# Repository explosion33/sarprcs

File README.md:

# sasrprcs
2023-2024 SARP RCS Controls / Electronics repository

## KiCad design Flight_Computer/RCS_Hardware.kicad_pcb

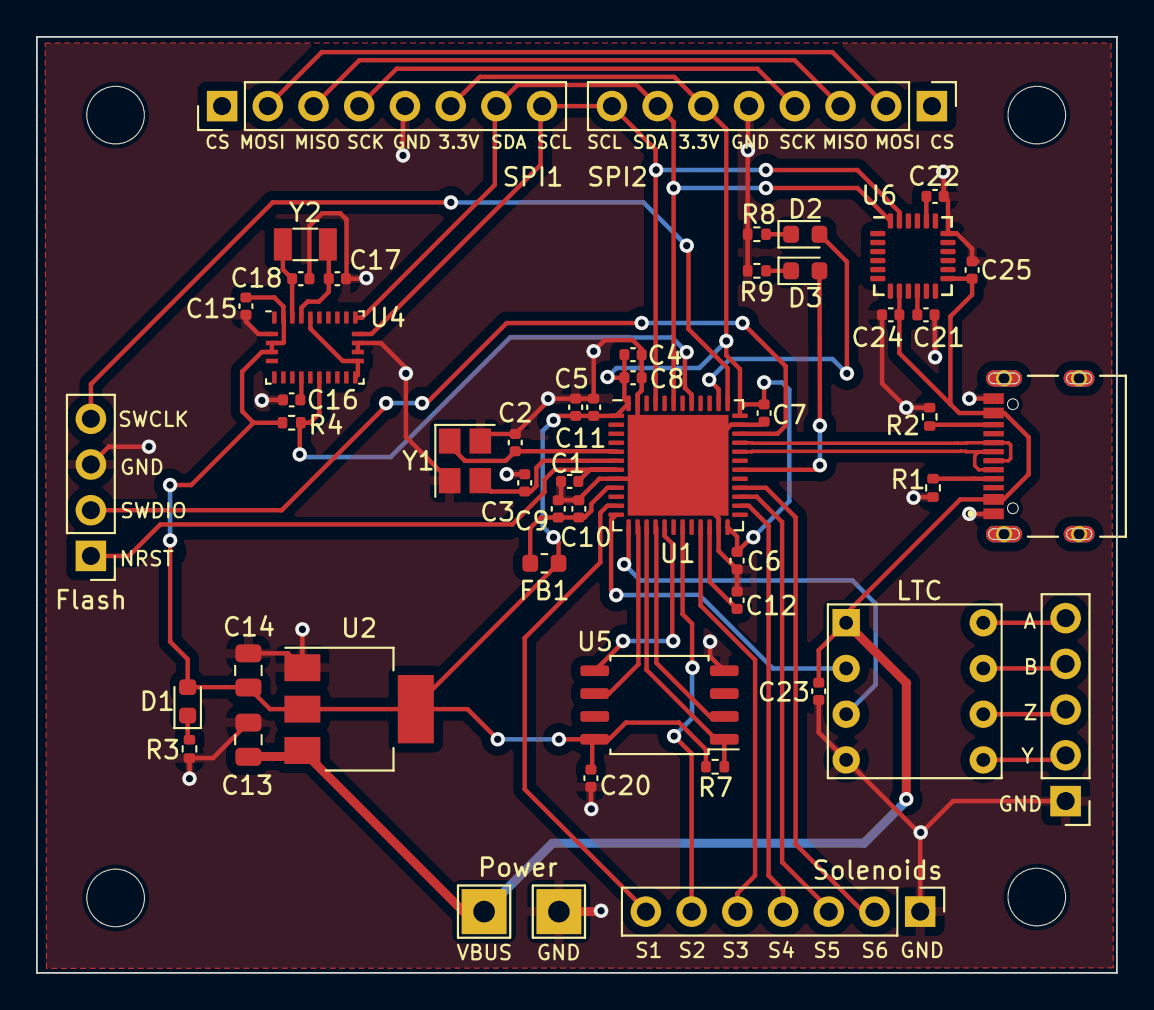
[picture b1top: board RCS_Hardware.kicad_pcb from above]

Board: 2 copper layers, 60.0 x 52.0 mm, 55 parts (0 on the bottom side), 47 nets.

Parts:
C1, C5, C6, C7, C8, C15, C16, C20, C23: 100nF; C_0402_1005Metric
C2, C3: 10pF; C_0402_1005Metric
C4: 10uF; C_0402_1005Metric
C9, C25: 10nF; C_0402_1005Metric
C10, C11: 1uF; C_0402_1005Metric
C12: 2.2uF; C_0402_1005Metric
C13, C14: 22uF; C_0805_2012Metric
C17, C18: 22pF; C_0402_1005Metric
C21, C24: 0.1uF; C_0402_1005Metric
C22: 2.2nF; C_0402_1005Metric
D1, D2, D3: LED; LED_0603_1608Metric
FB1: 120R; L_0603_1608Metric
Flash: SWD; PinHeader_1x04_P2.54mm_Vertical
H1, H2, H3, H4: MountingHole; MountingHole_3.2mm_M3
J2: TYPE-C-31-M-12; HRO_TYPE-C-31-M-12
J4: 5V; TestPoint_THTPad_2.5x2.5mm_Drill1.2mm
J8: Conn_01x05_Male; PinHeader_1x05_P2.54mm_Vertical
LTC: LTC1690N8
Power: GND; TestPoint_THTPad_2.5x2.5mm_Drill1.2mm
R1, R2: 5.11k; R_0402_1005Metric
R3, R8, R9: 1k; R_0402_1005Metric
R4, R7: 10k; R_0402_1005Metric
SPI1, SPI2: SPI; PinHeader_1x08_P2.54mm_Vertical
Solenoids: Solenoids; PinHeader_1x07_P2.54mm_Vertical
U1: STM32F401CCU6; QFN-48-1EP_7x7mm_P0.5mm_EP5.6x5.6mm
U2: AMS1117-3.3; SOT-223-3_TabPin2
U4: BNO055; LGA-28_5.2x3.8mm_P0.5mm
U5: W25Q32JVSS; SOIC-8_5.23x5.23mm_P1.27mm
U6: MPU-6050; InvenSense_QFN-24_4x4mm_P0.5mm
Y1: 16MHz; Crystal_SMD_3225-4Pin_3.2x2.5mm
Y2: 32.768Mhz; Crystal_SMD_3215-2Pin_3.2x1.5mm

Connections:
+3.3V: C4.1, C5.1, C6.1, C7.1, C8.1, C11.1, C14.1, C15.1, C20.1, D1.2 (A), FB1.2, R4.1, R7.1, SPI1.6, SPI2.6, U1.1 (VBAT), U1.24 (VDD), U1.36 (VDD), U1.48 (VDD), U2.2 (VO), U4.3 (VDD), U4.4 (~BOOT_LOAD_PIN), U4.28 (VDDIO), U5.8 (VCC)
+3.3VA: C9.1, C10.1, FB1.1, U1.9 (VREF+)
/BNO_NRST: R4.2, U1.41 (PB5), U4.11 (~RESET)
/CS_FLASH: U1.14 (PA4), U5.6 (CLK)
/LED_B: D3.2 (A), U1.30 (PA9)
/LED_G: D2.2 (A), U1.38 (PA15)
/MISO: U1.16 (PA6), U5.2 (DO(IO1))
/MISO2: SPI1.3, SPI2.3
/MOSI: U1.17 (PA7), U5.5 (DI(IO0))
/MOSI2: SPI1.2, SPI2.2
/NRST: C1.1, Flash.1, U1.7 (NRST)
/OSC_IN: C2.1, U1.5 (PH0), Y1.1
/OSC_OUT: C3.1, U1.6 (PH1), Y1.3
/PWR_LED_K: D1.1 (K), R3.1
/RX: LTC.2 (R), U1.12 (PA2)
/S1: Solenoids.7, U1.11 (PA1)
/S2: Solenoids.6, U1.19 (PB1)
/S3: Solenoids.5, U1.21 (PB10)
/S4: Solenoids.4, U1.26 (PB13)
/S5: Solenoids.3, U1.27 (PB14)
/S6: Solenoids.2, U1.28 (PB15)
/SCK: SPI1.4, SPI2.4
/SCL: SPI1.8, SPI2.8, U1.45 (PB8), U4.19 (COM1), U6.23 (SCL)
/SCLK: R7.2, U1.15 (PA5), U5.1 (~CS)
/SDA: SPI1.7, SPI2.7, U1.43 (PB7), U4.20 (COM0), U6.24 (SDA)
/SWCLK: Flash.4, U1.37 (PA14)
/SWDIO: Flash.2, U1.34 (PA13)
/TX: LTC.3 (D), U1.13 (PA3)
/USB_D+: J2.A6 (DP1), J2.B6 (DP2), U1.33 (PA12)
/USB_D-: J2.A7 (DN1), J2.B7 (DN2), U1.32 (PA11)
GND: C1.2, C2.2, C3.2, C4.2, C5.2, C6.2, C7.2, C8.2, C9.2, C10.2, C11.2, C12.2, C13.2, C14.2, C15.2, C16.2, C17.2, C18.2, C20.2, C21.2, C22.2, C23.2, C24.2, C25.1, Flash.3, J2.A1/B12 (GND), J2.B1/A12 (GND), J2.S1 (SHIELD), J2.S2 (SHIELD), J2.S3 (SHIELD), J2.S4 (SHIELD), J8.1, LTC.4 (GND), Power.1, R1.1, R2.1, R3.2, R8.2, R9.2, SPI1.5, SPI2.5, Solenoids.1, U1.8 (VSSA), U1.23 (VSS), U1.35 (VSS), U1.47 (VSS), U1.49 (VSS), U2.1 (GND), U4.2 (GND), U4.17 (COM3), U4.18 (COM2), U5.4 (GND), U6.18 (GND), Y1.2, Y1.4
unnamed: D2.1 (K), R8.1
unnamed: D3.1 (K), R9.1
unnamed: J2.A5 (CC1), R1.2
unnamed: J2.B5 (CC2), R2.2
unnamed: J8.2, LTC.5 (Y)
unnamed: J8.3, LTC.6 (Z)
unnamed: J8.4, LTC.7 (B)
unnamed: J8.5, LTC.8 (A)
unnamed: C12.1, U1.22 (VCAP1)
unnamed: C16.1, U4.9 (CAP)
unnamed: U4.15 (GNDIO), U4.16 (GNDIO), U4.25 (GNDIO)
unnamed: C18.1, U4.27 (XIN32), Y2.1
unnamed: C17.1, U4.26 (XOUT32), Y2.2
unnamed: C22.1, U6.20 (CPOUT)
unnamed: C21.1, U6.10 (REGOUT)
VBUS: C13.1, C23.1, C24.1, C25.2, J2.A4/B9 (VBUS), J2.B4/A9 (VBUS), J4.1, LTC.1 (VCC), U2.3 (VI), U6.8 (VLOGIC), U6.13 (VDD)

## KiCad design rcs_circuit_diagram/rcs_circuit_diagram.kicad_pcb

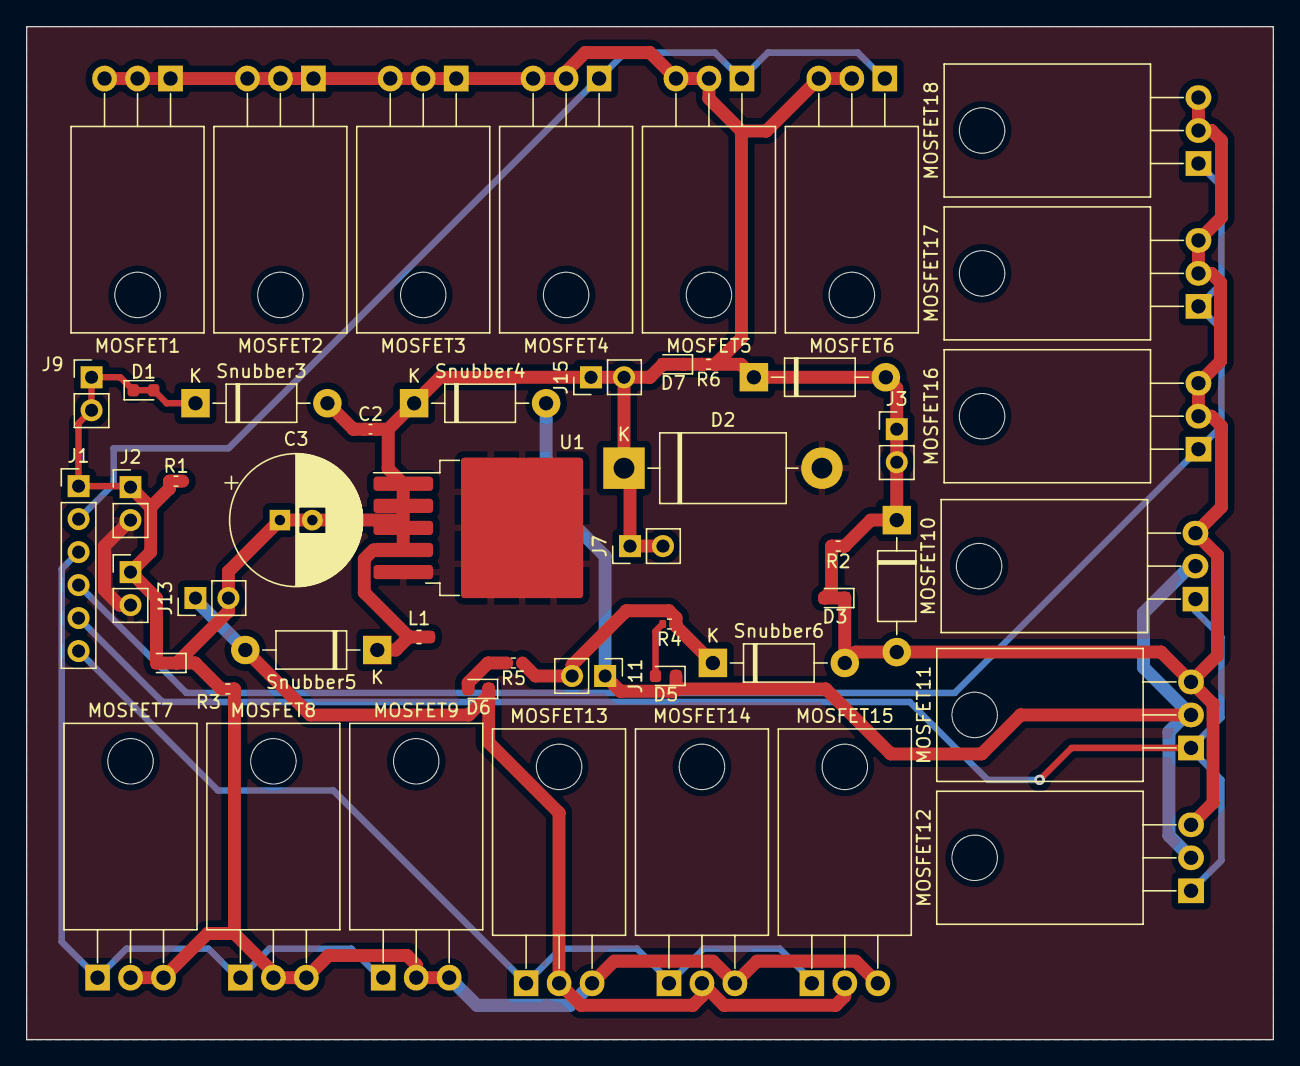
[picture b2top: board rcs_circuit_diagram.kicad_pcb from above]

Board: 2 copper layers, 96.0 x 78.0 mm, 50 parts (0 on the bottom side), 12 nets.

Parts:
C2: 220 uF; C_0402_1005Metric
C3: C_Polarized; CP_Radial_D10.0mm_P2.50mm
D1, D3, D4, D5, D6, D7: Red; LED_0603_1608Metric
D2: 1N5822; D_DO-201AD_P15.24mm_Horizontal
J1: Conn_01x06_Pin; PinHeader_1x06_P2.54mm_Vertical
J2, J3, J6, J7, J9, J11, J13, J15: Conn_01x02_Pin; PinHeader_1x02_P2.54mm_Vertical
L1: 33 uH; L_0603_1608Metric
MOSFET1, MOSFET2, MOSFET3, MOSFET4, MOSFET5, MOSFET6, MOSFET7, MOSFET8, MOSFET9, MOSFET10, MOSFET11, MOSFET12, MOSFET13, MOSFET14, MOSFET15, MOSFET16, MOSFET17, MOSFET18: IRLB8721; TO-220-3_Horizontal_TabDown
R1, R2, R3, R4, R5, R6: 4.7k; R_0402_1005Metric
Snubber1, Snubber2, Snubber3, Snubber4, Snubber5, Snubber6: 1N5819; D_DO-41_SOD81_P10.16mm_Horizontal
U1: LM2596S-5; TO-263-5_TabPin3

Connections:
/sol2: J1.2, MOSFET4.1 (G), MOSFET5.1 (G), MOSFET6.1 (G)
/sol3: J1.3, MOSFET7.1 (G), MOSFET8.1 (G), MOSFET9.1 (G)
/sol4: J1.4, MOSFET16.1 (G), MOSFET17.1 (G), MOSFET18.1 (G)
/sol5: J1.5, MOSFET10.1 (G), MOSFET11.1 (G), MOSFET12.1 (G)
/sol6: J1.6, MOSFET13.1 (G), MOSFET14.1 (G), MOSFET15.1 (G)
GND: D2.2 (A), J2.2, J6.2, U1.3 (GND), U1.5 (~ON/OFF)
unnamed: D5.2 (A), R4.2
unnamed: D5.1 (K), J11.1, MOSFET10.2 (D), MOSFET11.2 (D), MOSFET12.2 (D), Snubber4.2 (A)
unnamed: D6.2 (A), R5.2
unnamed: D6.1 (K), J13.1, MOSFET13.2 (D), MOSFET14.2 (D), MOSFET15.2 (D), Snubber5.2 (A)
unnamed: C2.1, C2.2, C3.1, C3.2, D1.1 (K), D1.2 (A), D2.1 (K), D3.1 (K), D3.2 (A), D4.1 (K), D4.2 (A), D7.1 (K), D7.2 (A), J1.1, J2.1, J3.1, J3.2, J6.1, J7.1, J7.2, J9.1, J9.2, J13.2, J15.1, J15.2, L1.1, L1.2, MOSFET1.1 (G), MOSFET1.2 (D), MOSFET1.3 (S), MOSFET2.1 (G), MOSFET2.2 (D), MOSFET2.3 (S), MOSFET3.1 (G), MOSFET3.2 (D), MOSFET3.3 (S), MOSFET4.2 (D), MOSFET4.3 (S), MOSFET5.2 (D), MOSFET5.3 (S), MOSFET6.2 (D), MOSFET6.3 (S), MOSFET7.2 (D), MOSFET7.3 (S), MOSFET8.2 (D), MOSFET8.3 (S), MOSFET9.2 (D), MOSFET9.3 (S), MOSFET10.3 (S), MOSFET11.3 (S), MOSFET12.3 (S), MOSFET13.3 (S), MOSFET14.3 (S), MOSFET15.3 (S), MOSFET16.2 (D), MOSFET16.3 (S), MOSFET17.2 (D), MOSFET17.3 (S), MOSFET18.2 (D), MOSFET18.3 (S), R1.1, R1.2, R2.1, R2.2, R3.1, R3.2, R6.1, R6.2, Snubber1.1 (K), Snubber1.2 (A), Snubber2.1 (K), Snubber2.2 (A), Snubber3.1 (K), Snubber3.2 (A), Snubber4.1 (K), Snubber5.1 (K), Snubber6.2 (A), U1.1 (VIN), U1.2 (OUT), U1.3 (GND), U1.4 (FB)
VCC: J11.2, R4.1, R5.1, Snubber6.1 (K)

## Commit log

2024-01-17 Initial Flight Computer Commit
2024-01-17 Initial Commit 2 (actual commit)
2024-01-18 Add Connections to MPU
2024-01-18 Added MPU Pin
2024-01-24 Create Power Supply
2024-01-24 Initial commit
    Copied solenoid circuit from capstone.
2024-01-24 Added ext. connectors
2024-01-24 Added voltage converter
2024-01-24 moved things around
2024-01-24 initial commit for lqr controller code
2024-01-28 Duplicated the circuit for each solenoid
2024-01-31 Cleaned up schematic
2024-02-02 adding lqr_controller.py
2024-02-02 adding simulation/summary plot
2024-02-07 Fixed power connection
2024-02-28 Added SPI/CS pins
2024-02-28 line
2024-04-17 Update rcs_circuit_diagram.kicad_sch
    Added footprints
2024-04-17 started new routing
2024-04-17 pcb layout started
2024-04-18 Rearranged components
2024-04-23 condensed pcb components
    haven't started actually routing yet--committing before that in case I mess it up.
2024-04-23 routed LEDs & LTC (no GND)
2024-04-24 expanded components & more routing
    60x60mm edge cut, ground copper fill layers.
2024-04-24 Updated footprints, changed layout of components
2024-04-25 Routing
2024-04-25 uhhhh more routing
2024-04-25 Flight Computer BOM
2024-04-25 more routing!
2024-04-26 Added BOM
2024-04-26 Everthing is routed
    ONLY errors/warnings for USB-C footprint and Ethan's awesome differential driver footprint.
2024-04-26 edited differential driver/receiver footprint
2024-04-26 moved some stuff around to aesthetics
    moved linear reg down, bottom edge cut & holes up.
2024-04-27 Everything is very much not right
2024-04-27 deleted all traces and started routing again
2024-04-27 Finished routing, 1mm traces
2024-04-28 uploaded 3d model for components
    UCB-C, LTC and Flash Storage
2024-04-29 horizon detection
2024-04-29 moved SPI connectors down & labeled all pins
2024-04-29 Branding on Back Silckscreen
2024-04-30 Update gitignore
2024-05-01 Clean up some code
2024-05-08 Started PID controller (python)
2024-05-11 started simulation & physics.py
2024-05-11 put in 1-DoF physics for sim, not yet functional
2024-05-11 simulation functional, needs tuning
2024-05-11 functional 1D sim with plot
2024-05-12 mildly tuned
2024-05-13 3DoF functional, physics might be wack
2024-05-14 physics are not wack
2024-05-16 started porting PID class to C++
2024-05-16 started matrix multiplication and simulation files
2024-05-17 initialized physics.cpp & simulation.cpp
2024-05-19 PID now outputs thruster on-time
2024-05-19 cool colors B)
2024-05-20 tuned z_controller (still preliminary)
2024-05-20 if statements for setting solenoid ontime
2024-05-20 changed time.time() to sim_time in ontime checks
2024-05-21 HOLY SHIT IT WORKS
    Made actuator class and fixed jitter actuation (it is 3:34am)
2024-05-21 commented/removed one of the actuator checks
2024-05-23 modified Actuator.getState method
2024-05-23 made Actuator.cpp & .h and modified PID class
    C++ code now kinda matches python script.
2024-05-23 fixed structure of main.cpp
    moved function definitions outside main()
2024-05-23 main.cpp outputs commands in a loop
2024-07-28 Added JLCPCB Part numbers to missing schemas Changed JLCPCB# to LSCS Part Adjusted silkscreen for some labels Added Payload LOGO to back silkscreen Generated manufacturing and assembly files
